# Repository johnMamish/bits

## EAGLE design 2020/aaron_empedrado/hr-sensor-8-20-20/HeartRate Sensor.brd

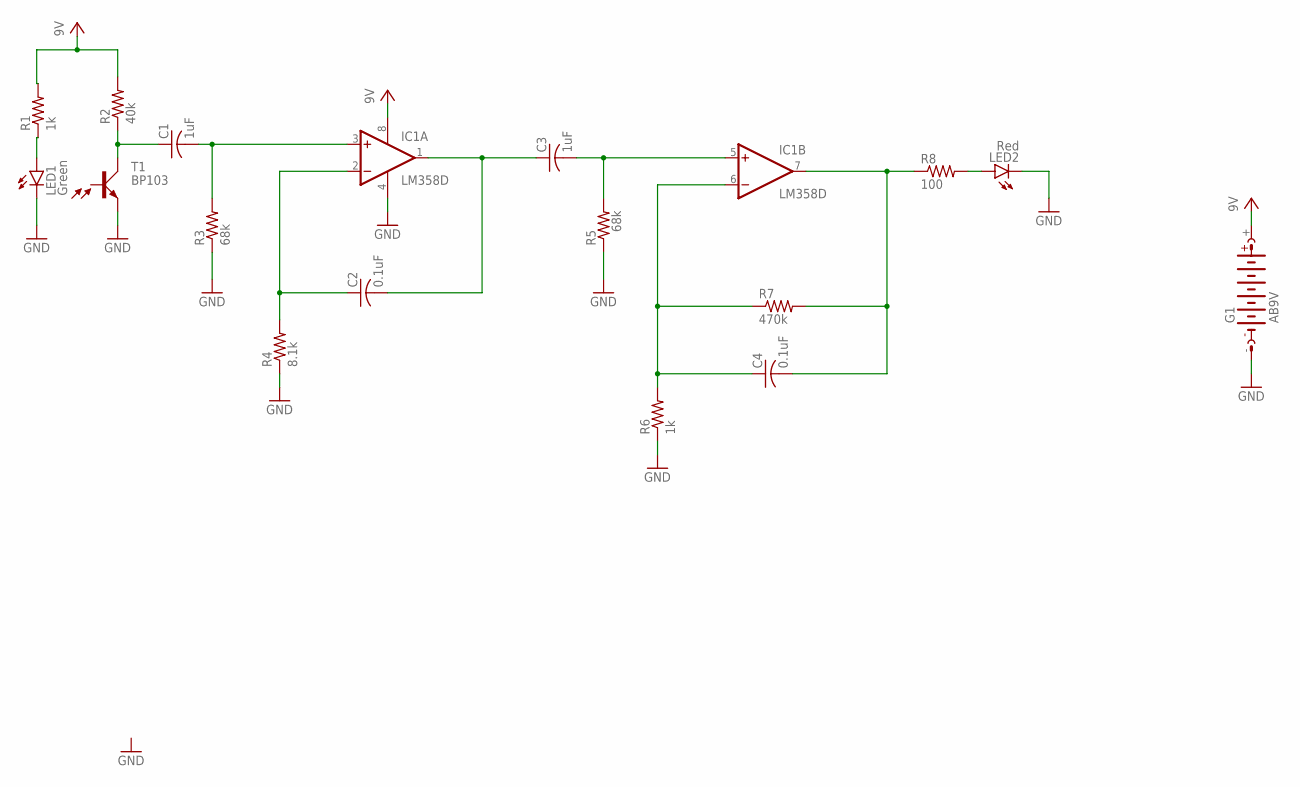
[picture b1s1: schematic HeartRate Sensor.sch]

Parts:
C1, C3: 1uF; C0805
C2, C4: 0.1uF; C0805
G1: AB9V
IC1: LM358D; SO08
LED1: Green; SMARTLED-TTW
LED2: Red; SMARTLED-TTW
R1, R6: 1k; R0805
R2: 40k; R0805
R3, R5: 68k; R0805
R4: 8.1k; R0805
R7: 470k; R0805
R8: 100; R0805
T1: BP103

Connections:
GND: G1.-, IC1.4 (V-), LED1.C@1 (C), LED2.C@1 (C), R3.1, R4.1, R5.1, R6.1, T1.E
unnamed: C1.2, IC1.3 (+IN), R3.2
unnamed: C2.1, IC1.2 (-IN), R4.2
unnamed: C3.2, IC1.5 (+IN), R5.2
unnamed: C2.2, C3.1, IC1.1 (OUT)
unnamed: C4.1, IC1.6 (-IN), R6.2, R7.1
unnamed: C4.2, IC1.7 (OUT), R7.2, R8.1
unnamed: LED2.A@1 (A), R8.2
unnamed: LED1.A@1 (A), R1.1
unnamed: C1.1, R2.1, T1.C
VCC: G1.+, IC1.8 (V+), R1.2, R2.2

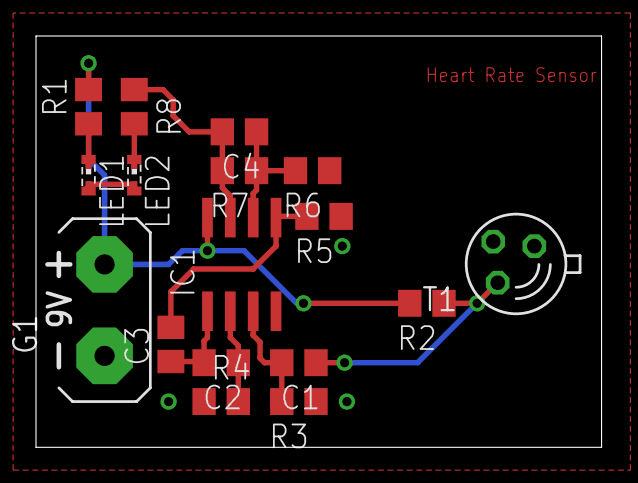
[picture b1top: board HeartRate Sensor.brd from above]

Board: 2 copper layers, 31.4 x 22.9 mm, 17 parts (0 on the bottom side), 11 nets.

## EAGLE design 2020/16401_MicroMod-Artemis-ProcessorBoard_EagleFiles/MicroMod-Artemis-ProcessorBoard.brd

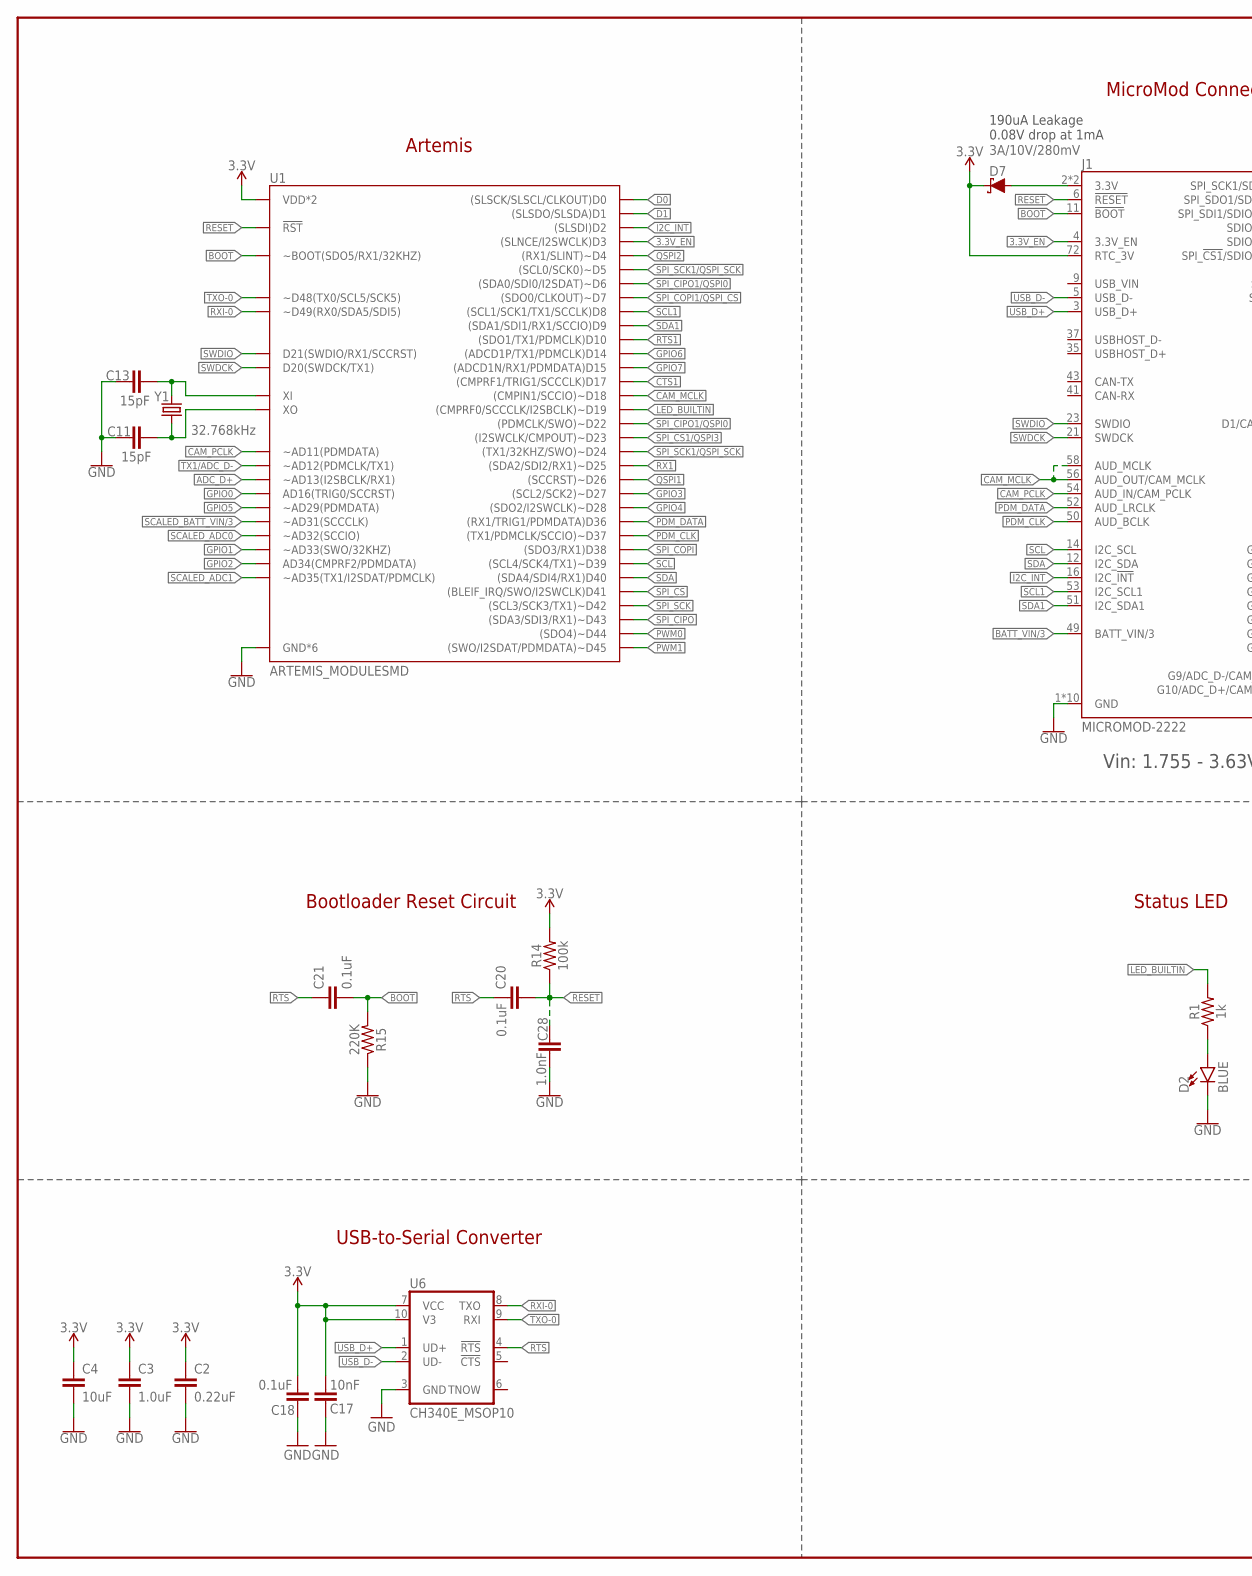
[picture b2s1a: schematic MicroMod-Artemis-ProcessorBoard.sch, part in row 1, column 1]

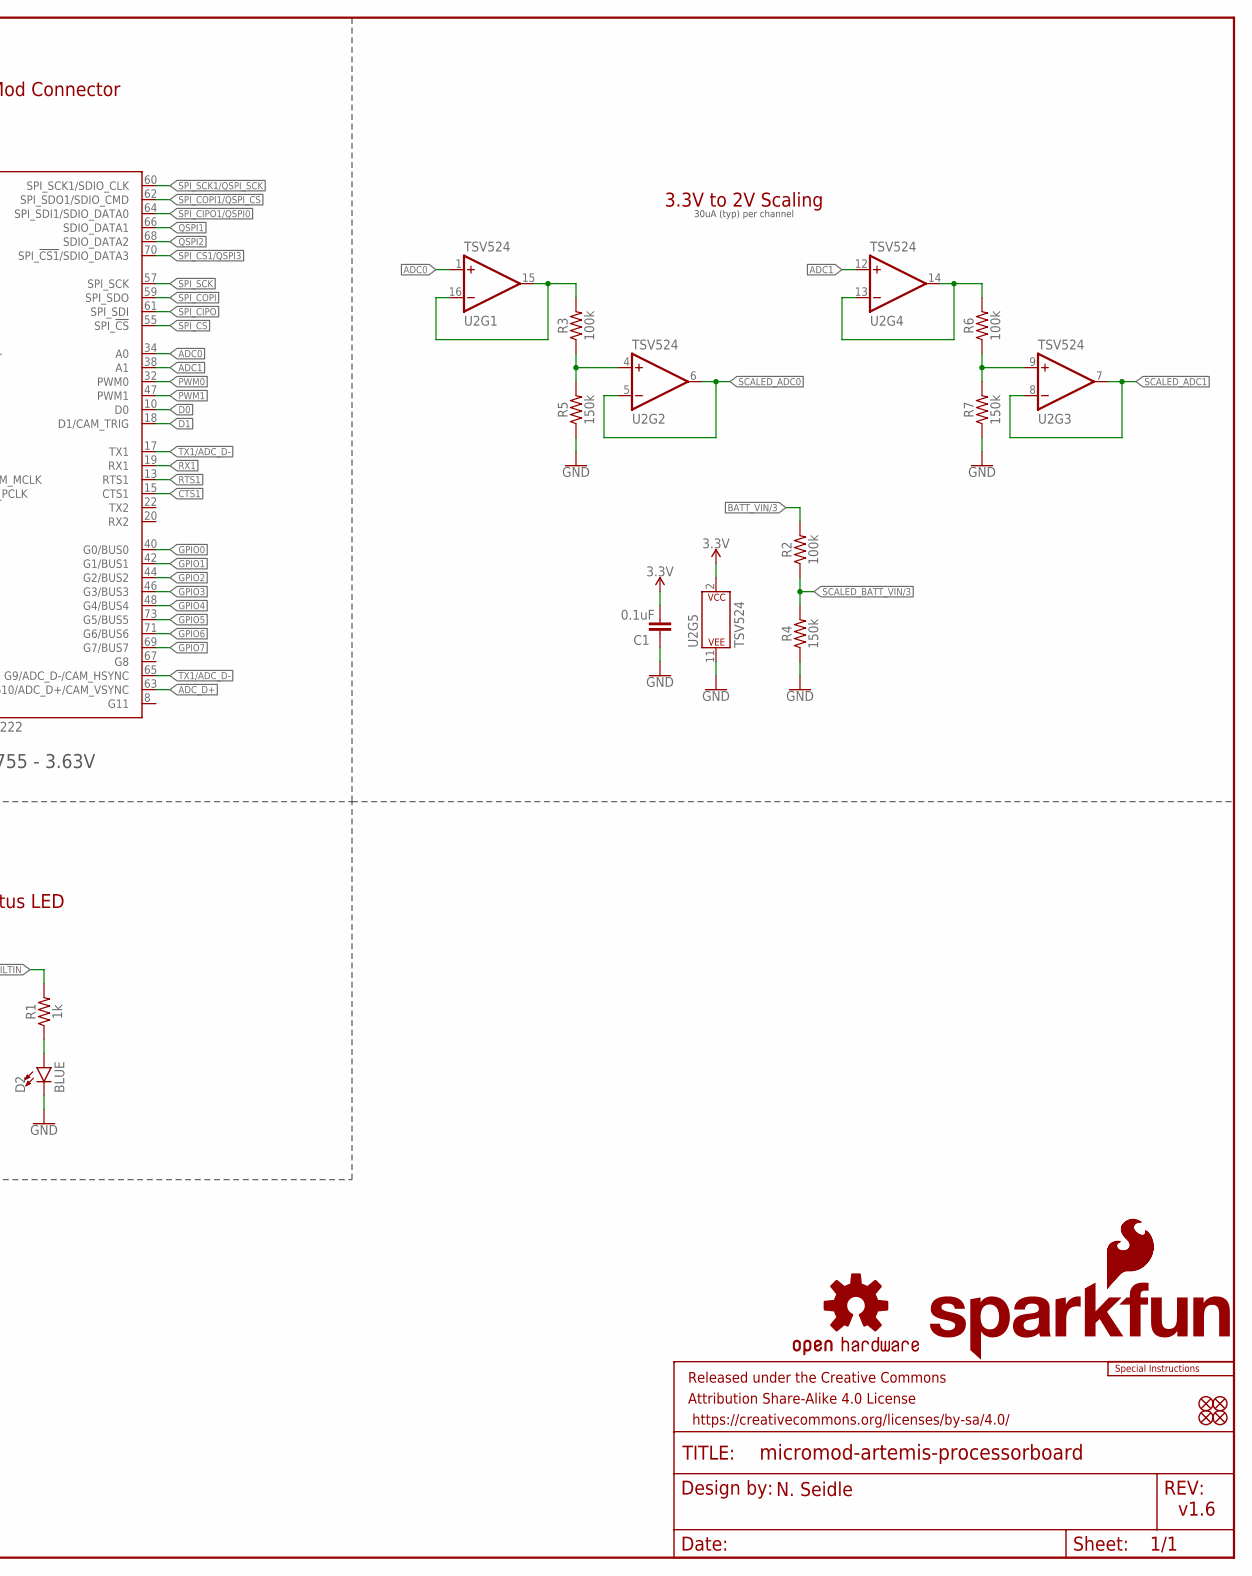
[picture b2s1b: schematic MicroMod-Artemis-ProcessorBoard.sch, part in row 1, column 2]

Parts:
C1, C18, C20, C21: 0.1uF; 0402-TIGHT
C2: 0.22uF; 0402-TIGHT
C3: 1.0uF; 0402-TIGHT
C4: 10uF; 0603
C11, C13: 15pF; 0402-TIGHT
C17: 10nF; 0402-TIGHT
C28: 1.0nF; 0402-TIGHT
D2: BLUE; LED-0603
D7: 3A/10V/280mV; SOD-323
FD1, FD2, FD3, FD4: FIDUCIALUFIDUCIAL; FIDUCIAL-MICRO
FRAME1: FRAME-LEDGER; CREATIVE_COMMONS
J1: MICROMOD-2222; M.2-CARD-E-22
LOGO1: SFE_LOGO_NAME_FLAME.1_INCH; SFE_LOGO_NAME_FLAME_.1
LOGO2: SFE_LOGO_FLAME.1_INCH; SFE_LOGO_FLAME_.1
LOGO3: OSHW-LOGOMINI; OSHW-LOGO-MINI
LOGO4: SPECIAL_INSTRUCTIONS-ORDERING; ORDERING_INSTRUCTIONS
R1: 1k; 0402-TIGHT
R2, R3, R6, R14: 100k; 0402-TIGHT
R4, R5, R7: 150k; 0402-TIGHT
R15: 220K; 0402-TIGHT
U1: ARTEMIS_MODULESMD; ARTEMIS_FP
U2: TSV524; QFN-16
U6: CH340E_MSOP10; MSOP10
Y1: 32.768kHz; CRYSTAL-SMD-3.2X1.5MM

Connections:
3.3V: C1.1, C2.1, C3.1, C4.1, C17.1, C18.1, D7.C, J1.72 (RTC_3V), R14.2, U1.VDD@36 (VDD*2), U1.VDD@37 (VDD*2), U2.2 (V+), U6.7 (VCC), U6.10 (V3)
3.3V_EN: J1.4 (3.3V_EN), U1.D3 ((SLNCE/I2SWCLK)D3)
3.3V_MAIN: D7.A, J1.2 (3.3V), J1.74 (3.3V)
!RESET!: C20.2, C28.1, J1.6 (!RESET!), R14.1, U1.~RST (!RST)
!RTS: C20.1, C21.1, U6.4 (!RTS)
ADC0: J1.34 (A0), U2.1 (+IN)
ADC0_BUFF1: R3.2, U2.15 (OUT), U2.16 (-IN)
ADC0_BUFF2: R3.1, R5.2, U2.4 (+IN)
ADC1: J1.38 (A1), U2.12 (+IN)
ADC1_BUFF2: R6.1, R7.2, U2.9 (+IN)
ADC_BUFF1: R6.2, U2.13 (-IN), U2.14 (OUT)
ADC_D+: J1.63 (G10/ADC_D+/CAM_VSYNC), U1.~AD13 (~AD13(I2SBCLK/RX1))
BATT_VIN/3: J1.49 (BATT_VIN/3), R2.2
BOOT: C21.2, J1.11 (!BOOT!), R15.2, U1.BOOT (~BOOT(SDO5/RX1/32KHZ))
CAM_MCLK: J1.56 (AUD_OUT/CAM_MCLK), J1.58 (AUD_MCLK), U1.~D18 ((CMPIN1/SCCIO)~D18)
CAM_PCLK: J1.54 (AUD_IN/CAM_PCLK), U1.~AD11 (~AD11(PDMDATA))
CTS1: J1.15 (CTS1), U1.D17 ((CMPRF1/TRIG1/SCCCLK)D17)
D0: J1.10 (D0), U1.D0 ((SLSCK/SLSCL/CLKOUT)D0)
D1: J1.18 (D1/CAM_TRIG), U1.D1 ((SLSDO/SLSDA)D1)
GND: C1.2, C2.2, C3.2, C4.2, C11.1, C13.1, C17.2, C18.2, C28.2, D2.C, J1.1 (GND), J1.7 (GND), J1.33 (GND), J1.36 (GND), J1.39 (GND), J1.45 (GND), J1.75 (GND), J1.GND1 (GND), J1.GND2 (GND), J1.GND3 (GND), R4.1, R5.1, R7.1, R15.1, U1.GND@1 (GND*6), U1.GND@22 (GND*6), U1.GND@38 (GND*6), U1.GND@39 (GND*6), U1.GND@47 (GND*6), U1.GND@59 (GND*6), U2.11 (V-), U6.3 (GND)
GPIO0: J1.40 (G0/BUS0), U1.AD16 (AD16(TRIG0/SCCRST))
GPIO1: J1.42 (G1/BUS1), U1.~AD33/SWO (~AD33(SWO/32KHZ))
GPIO2: J1.44 (G2/BUS2), U1.AD34 (AD34(CMPRF2/PDMDATA))
GPIO3: J1.46 (G3/BUS3), U1.~D27 ((SCL2/SCK2)~D27)
GPIO4: J1.48 (G4/BUS4), U1.~D28 ((SDO2/I2SWCLK)~D28)
GPIO5: J1.73 (G5/BUS5), U1.~AD29 (~AD29(PDMDATA))
GPIO6: J1.71 (G6/BUS6), U1.D14 ((ADCD1P/TX1/PDMCLK)D14)
GPIO7: J1.69 (G7/BUS7), U1.D15 ((ADCD1N/RX1/PDMDATA)D15)
I2C_!INT!: J1.16 (I2C_!INT!), U1.D2 ((SLSDI)D2)
LED_BUILTIN: R1.2, U1.~D19 ((CMPRF0/SCCCLK/I2SBCLK)~D19)
unnamed: D2.A, R1.1
unnamed: C13.2, U1.XI, Y1.P$1 (1)
unnamed: C11.2, U1.XO, Y1.P$2 (2)
PDM_CLK: J1.50 (AUD_BCLK), U1.~D37 ((TX1/PDMCLK/SCCIO)~D37)
PDM_DATA: J1.52 (AUD_LRCLK), U1.D36 ((RX1/TRIG1/PDMDATA)D36)
PWM0: J1.32 (PWM0), U1.~D44 ((SDO4)~D44)
PWM1: J1.47 (PWM1), U1.~D45 ((SWO/I2SDAT/PDMDATA)~D45)
QSPI1: J1.66 (SDIO_DATA1), U1.~D26 ((SCCRST)~D26)
QSPI2: J1.68 (SDIO_DATA2), U1.~D4 ((RX1/SLINT)~D4)
RTS1: J1.13 (RTS1), U1.D10 ((SDO1/TX1/PDMCLK)D10)
RX1: J1.19 (RX1), U1.~D25 ((SDA2/SDI2/RX1)~D25)
RXI-0: U1.RXI-0 (~D49(RX0/SDA5/SDI5)), U6.8 (TXO)
SCALED_ADC0: U1.~AD32 (~AD32(SCCIO)), U2.5 (-IN), U2.6 (OUT)
SCALED_ADC1: U1.~AD35 (~AD35(TX1/I2SDAT/PDMCLK)), U2.7 (OUT), U2.8 (-IN)
SCALED_BATT_VIN/3: R2.1, R4.2, U1.~AD31 (~AD31(SCCCLK))
SCL: J1.14 (I2C_SCL), U1.~D39 ((SCL4/SCK4/TX1)~D39)
SCL1: J1.53 (I2C_SCL1), U1.D8 ((SCL1/SCK1/TX1/SCCLK)D8)
SDA: J1.12 (I2C_SDA), U1.D40 ((SDA4/SDI4/RX1)D40)
SDA1: J1.51 (I2C_SDA1), U1.D9 ((SDA1/SDI1/RX1/SCCIO)D9)
SPI_!CS1!/QSPI3: J1.70 (SPI_!CS1!/SDIO_DATA3), U1.~D23 ((I2SWCLK/CMPOUT)~D23)
SPI_!CS!: J1.55 (SPI_!CS!), U1.D41 ((BLEIF_IRQ/SWO/I2SWCLK)D41)
SPI_CIPO: J1.61 (SPI_SDI), U1.~D43 ((SDA3/SDI3/RX1)~D43)
SPI_CIPO1/QSPI0: J1.64 (SPI_SDI1/SDIO_DATA0), U1.~D6 ((SDA0/SDI0/I2SDAT)~D6), U1.~D22 ((PDMCLK/SWO)~D22)
SPI_COPI: J1.59 (SPI_SDO), U1.D38 ((SDO3/RX1)D38)
SPI_COPI1/QSPI_!CS!: J1.62 (SPI_SDO1/SDIO_CMD), U1.D7 ((SDO0/CLKOUT)~D7)
SPI_SCK: J1.57 (SPI_SCK), U1.~D42 ((SCL3/SCK3/TX1)~D42)
SPI_SCK1/QSPI_SCK: J1.60 (SPI_SCK1/SDIO_CLK), U1.~D5 ((SCL0/SCK0)~D5), U1.~D24 ((TX1/32KHZ/SWO)~D24)
SWDCK: J1.21 (SWDCK), U1.SWDCK (D20(SWDCK/TX1))
SWDIO: J1.23 (SWDIO), U1.SWDIO (D21(SWDIO/RX1/SCCRST))
TX1/ADC_D-: J1.17 (TX1), J1.65 (G9/ADC_D-/CAM_HSYNC), U1.~AD12 (~AD12(PDMCLK/TX1))
TXO-0: U1.TXO-0 (~D48(TX0/SCL5/SCK5)), U6.9 (RXI)
USB_D+: J1.3 (USB_D+), U6.1 (UD+)
USB_D-: J1.5 (USB_D-), U6.2 (UD-)

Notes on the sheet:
USB-to-Serial Converter
Bootloader Reset Circuit
MicroMod Connector
3.3V to 2V Scaling
v1.6
N. Seidle
Artemis
Status LED
Vin: 1.755 - 3.63V
190uA Leakage 0.08V drop at 1mA
30uA (typ) per channel

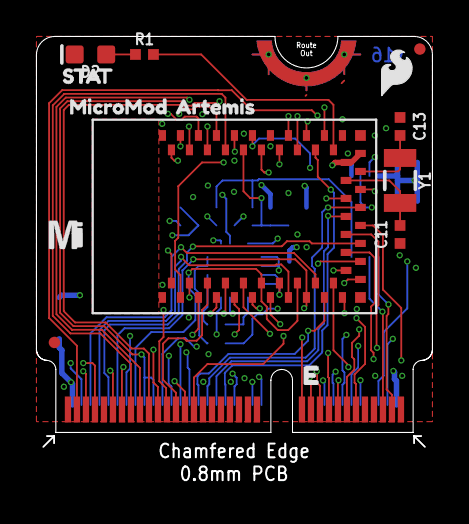
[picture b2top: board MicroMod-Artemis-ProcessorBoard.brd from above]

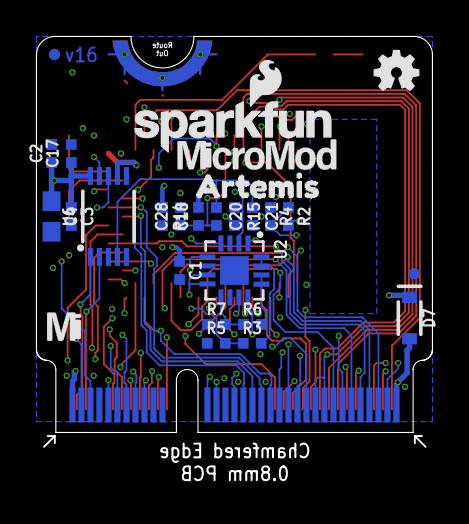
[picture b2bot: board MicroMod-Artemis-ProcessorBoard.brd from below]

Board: 4 copper layers, 21.9 x 25.0 mm, 43 parts (27 on the bottom side), 63 nets.

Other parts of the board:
U$1, U$7: MICROMOD_MI_LOGO_.35
U$2: ARTEMIS0
U$3: MICROMOD1
U$4: STAT_TO_32
U$5: MICROMOD_LOGO_.35
U$6: ARTEMIS2

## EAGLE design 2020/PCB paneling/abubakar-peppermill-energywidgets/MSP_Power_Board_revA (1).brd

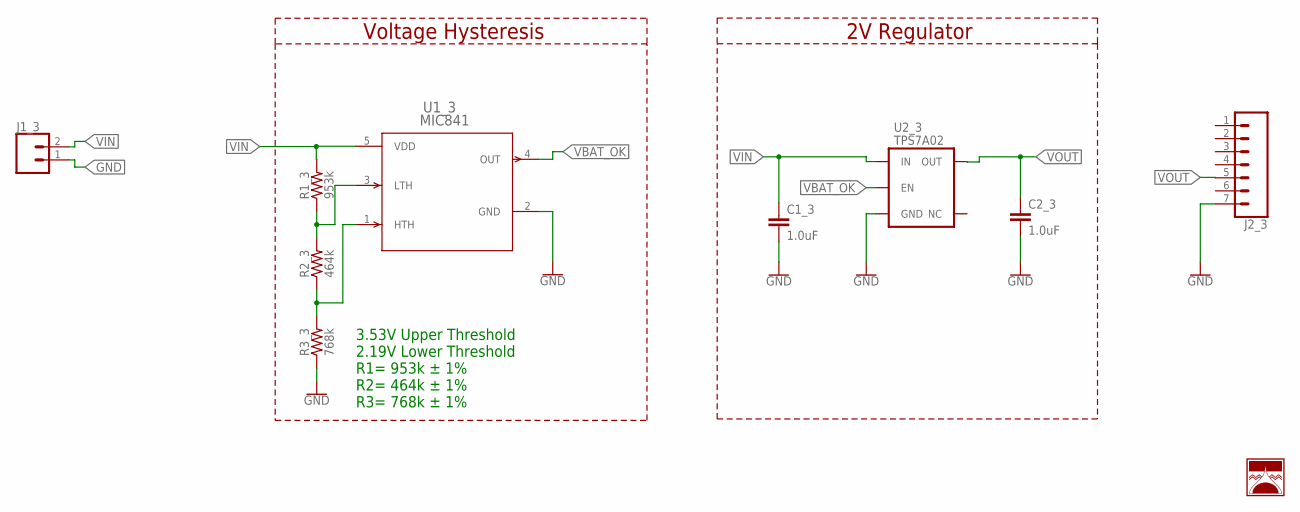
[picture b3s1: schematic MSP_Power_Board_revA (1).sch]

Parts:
C1_3, C2_3: 1.0uF; 0603
J1_3: CONN_02; 1X02
J2_3: CONN_07; 1X07
R1_3: 953k; 0603
R2_3: 464k; 0603
R3_3: 768k; 0603
U1_3: MIC841; SC-70_C5_MCH
U2_3: TPS7A02; SOT23-5
U$1_3: KAMOAMOA_LOGO_4X4MM; LOGO_4X4MM

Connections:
GND: C1_3.2, C2_3.2, J1_3.1, J2_3.7, R3_3.1, U1_3.2 (GND), U2_3.2 (GND)
unnamed: R1_3.1, R2_3.2, U1_3.3 (LTH)
unnamed: R2_3.1, R3_3.2, U1_3.1 (HTH)
VBAT_OK: U1_3.4 (OUT), U2_3.3 (EN)
VIN: C1_3.1, J1_3.2, R1_3.2, U1_3.5 (VDD), U2_3.1 (IN)
VOUT: C2_3.1, J2_3.5, U2_3.5 (OUT)

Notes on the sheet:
Voltage Hysteresis
3.53V Upper Threshold 2.19V Lower Threshold R1= 953k ± 1% R2= 464k ± 1% R3= 768k ± 1%
2V Regulator

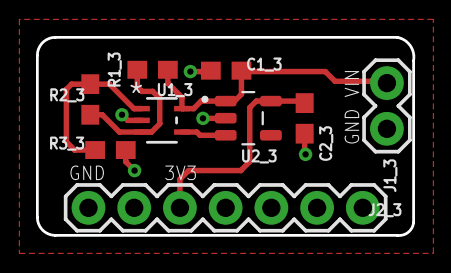
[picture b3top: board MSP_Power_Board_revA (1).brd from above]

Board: 2 copper layers, 20.9 x 11.0 mm, 10 parts (0 on the bottom side), 6 nets.

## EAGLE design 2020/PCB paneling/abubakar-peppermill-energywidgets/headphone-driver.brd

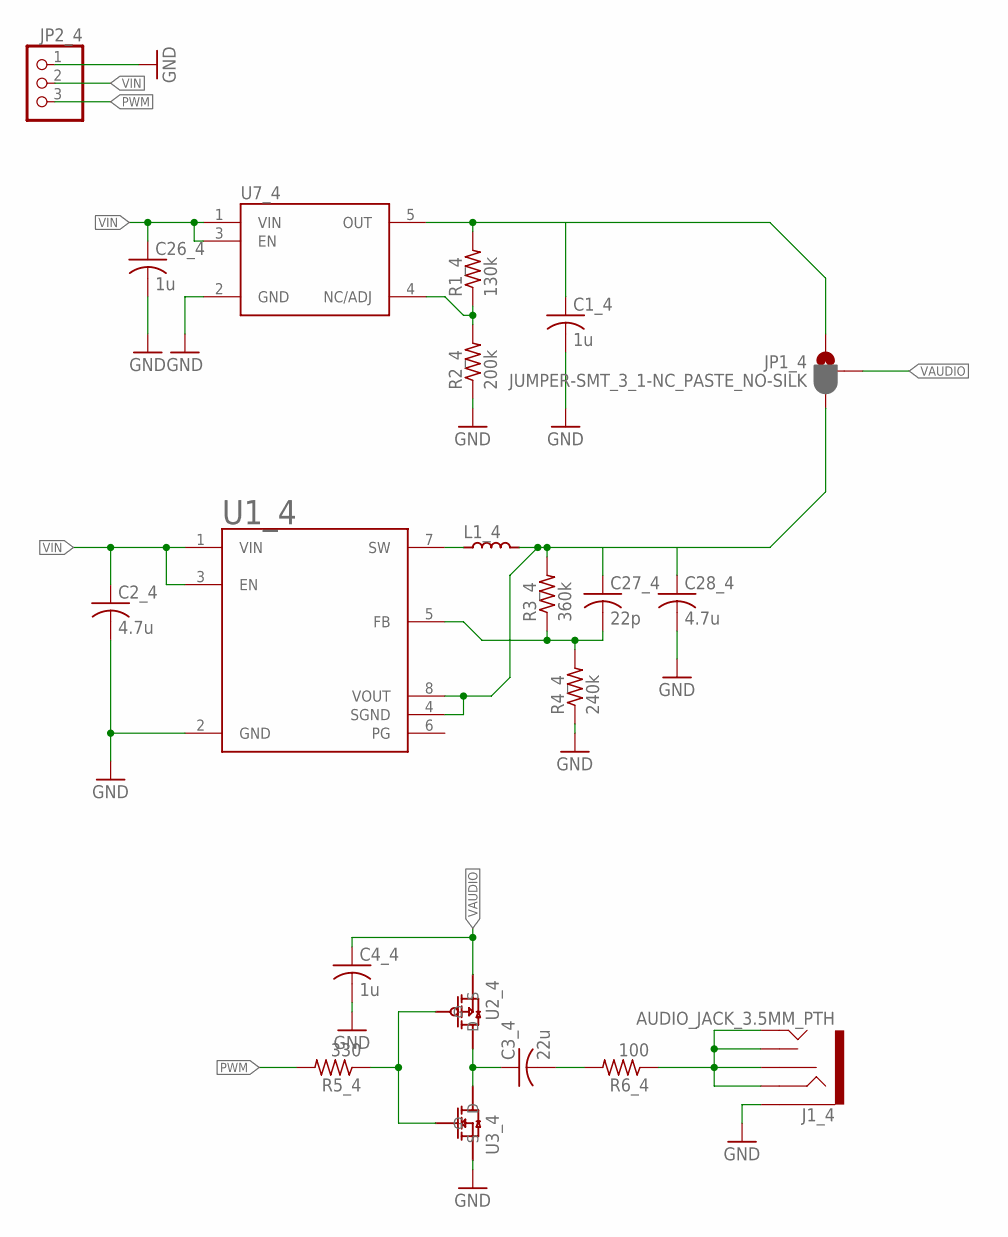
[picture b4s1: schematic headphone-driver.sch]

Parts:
C1_4, C4_4, C26_4: 1u; C0603; MFR_PN CL10B105KA8NNNC
C2_4, C28_4: 4.7u; C0603; MFR_PN CL10A475KA8NQNC
C3_4: 22u; C0805; MFR_PN GRM21BR61E226ME44L
C27_4: 22p; C0402; MFR_PN C0603C220J5GACTU
J1_4: AUDIO_JACK_3.5MM_PTH; AUDIO-JACK
JP1_4: JUMPER-SMT_3_1-NC_PASTE_NO-SILK; SMT-JUMPER_3_1-NC_PASTE_NO-SILK
JP2_4: PINHD-1X3; 1X03
L1_4: 22u; LQH3NPNXXXXMEX; MFR_PN LQH3NPN220MJRL
R1_4: 130k; R0603; MFR_PN ERJ-3GEYJ134V
R2_4: 200k; R0603; MFR_PN ERJ-3GEYJ204V
R3_4: 360k; R0603; MFR_PN ERJ-3GEYJ364V
R4_4: 240k; R0603; MFR_PN ERJ-3GEYJ244V
R5_4: 330; R0603; MFR_PN RC0603FR-07330RL
R6_4: 100; R0603; MFR_PN RC0603JR-07100RL
U1_4: TPS62120; SOP65P280X145-8N; MFR_PN TPS62120
U2_4: TP2104K1-G
U3_4: TN2106K1-G
U7_4: MIC5225; MFR_PN MIC5225YM5

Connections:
BUCK_OUT: C27_4.1, C28_4.1, JP1_4.3, L1_4.P$2, R3_4.2, U1_4.4 (SGND), U1_4.8 (VOUT)
GND: C1_4.2, C2_4.2, C4_4.2, C26_4.2, C28_4.2, J1_4.SLEEVE, JP2_4.1, R2_4.1, R4_4.1, U1_4.2 (GND), U3_4.S, U7_4.2 (GND)
LINEAR_OUT: C1_4.1, JP1_4.1, R1_4.2, U7_4.5 (OUT)
unnamed: R1_4.1, R2_4.2, U7_4.4 (NC/ADJ)
unnamed: R5_4.1, U2_4.G, U3_4.G
unnamed: C3_4.1, U2_4.D, U3_4.D
unnamed: C27_4.2, R3_4.1, R4_4.2, U1_4.5 (FB)
unnamed: L1_4.P$1, U1_4.7 (SW)
unnamed: C3_4.2, R6_4.2
unnamed: J1_4.RING, J1_4.RSH, J1_4.TIP, J1_4.TSH, R6_4.1
PWM: JP2_4.3, R5_4.2
VAUDIO: C4_4.1, JP1_4.2, U2_4.S
VIN: C2_4.1, C26_4.1, JP2_4.2, U1_4.1 (VIN), U1_4.3 (EN), U7_4.1 (VIN), U7_4.3 (EN)

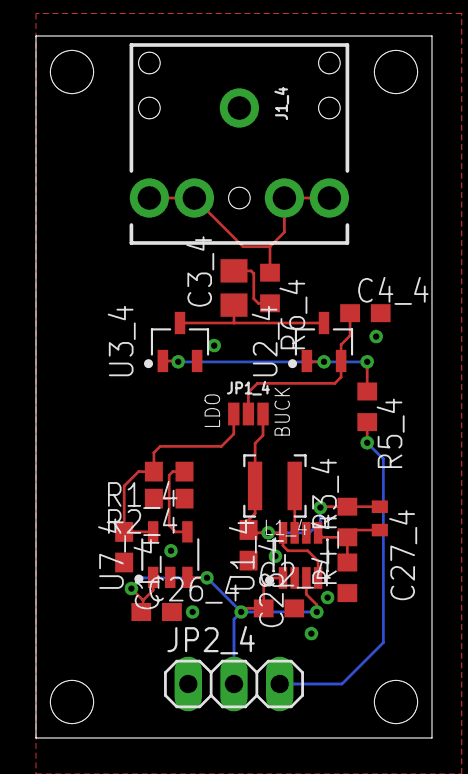
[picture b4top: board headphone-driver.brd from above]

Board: 2 copper layers, 22.0 x 39.0 mm, 21 parts (0 on the bottom side), 13 nets.

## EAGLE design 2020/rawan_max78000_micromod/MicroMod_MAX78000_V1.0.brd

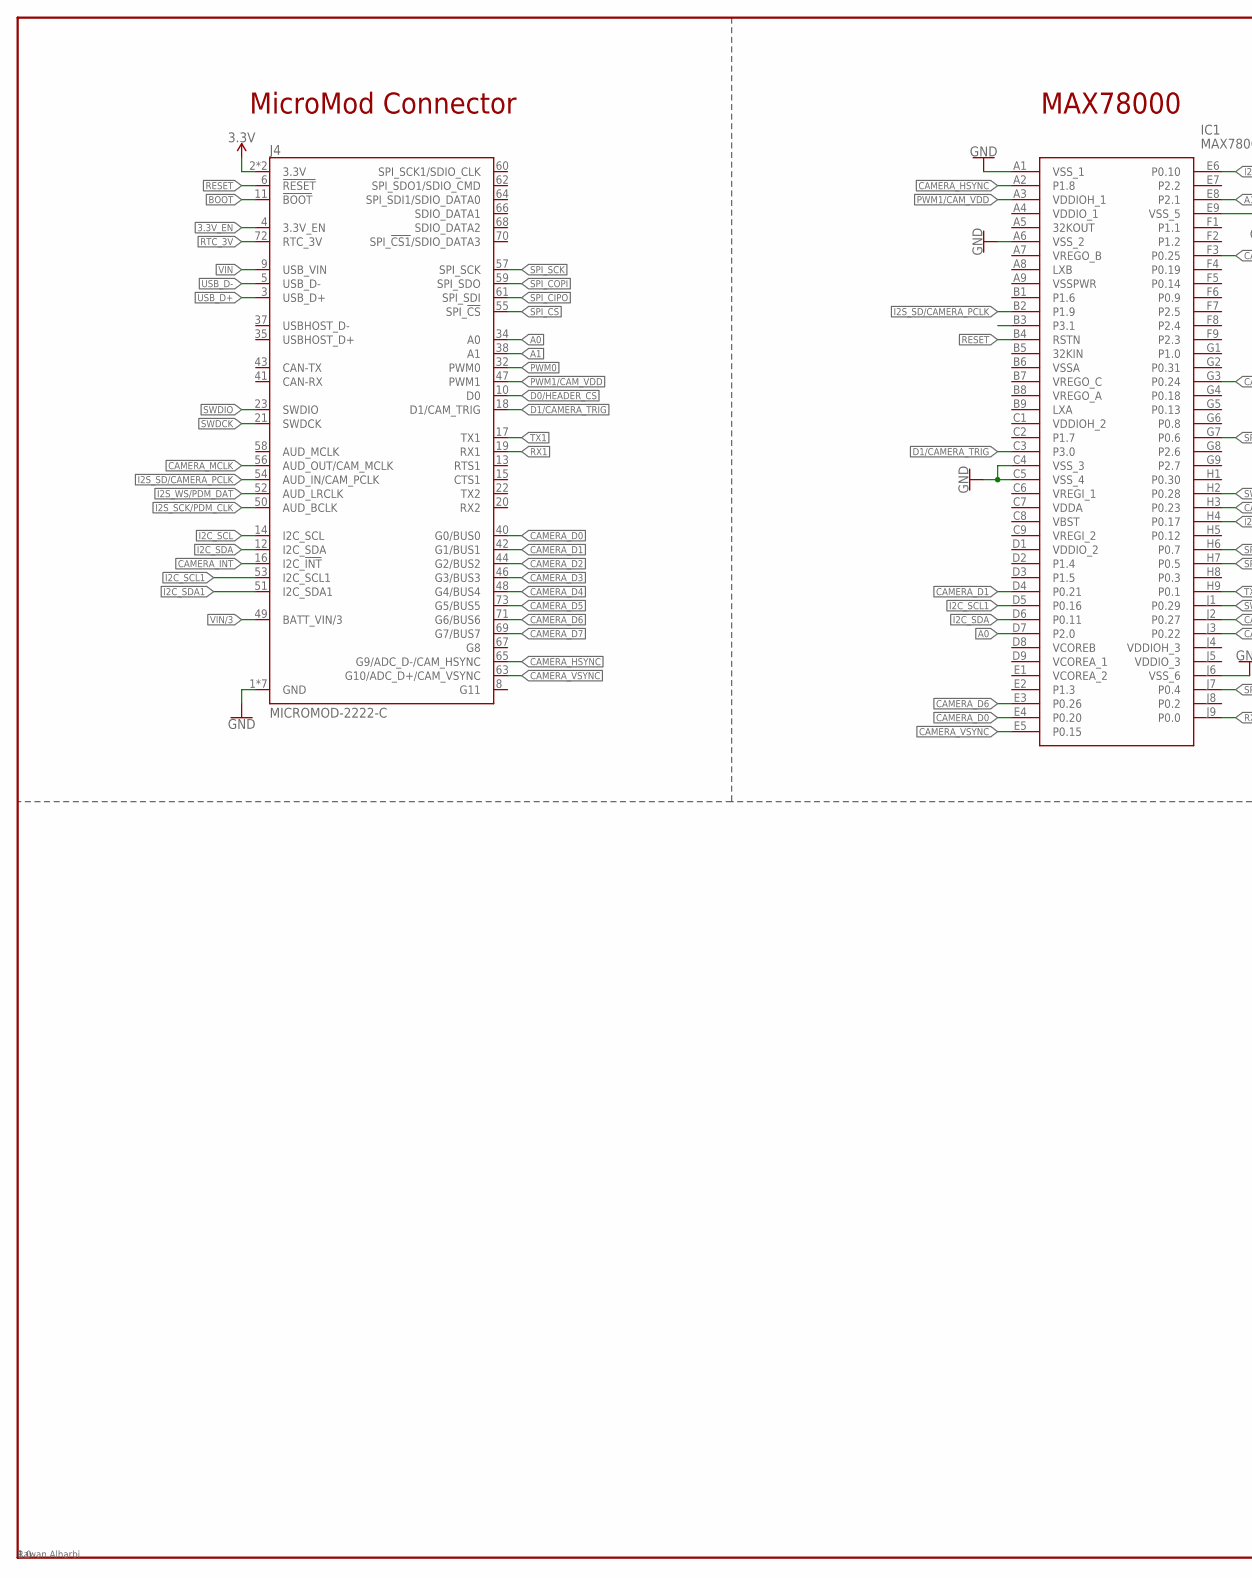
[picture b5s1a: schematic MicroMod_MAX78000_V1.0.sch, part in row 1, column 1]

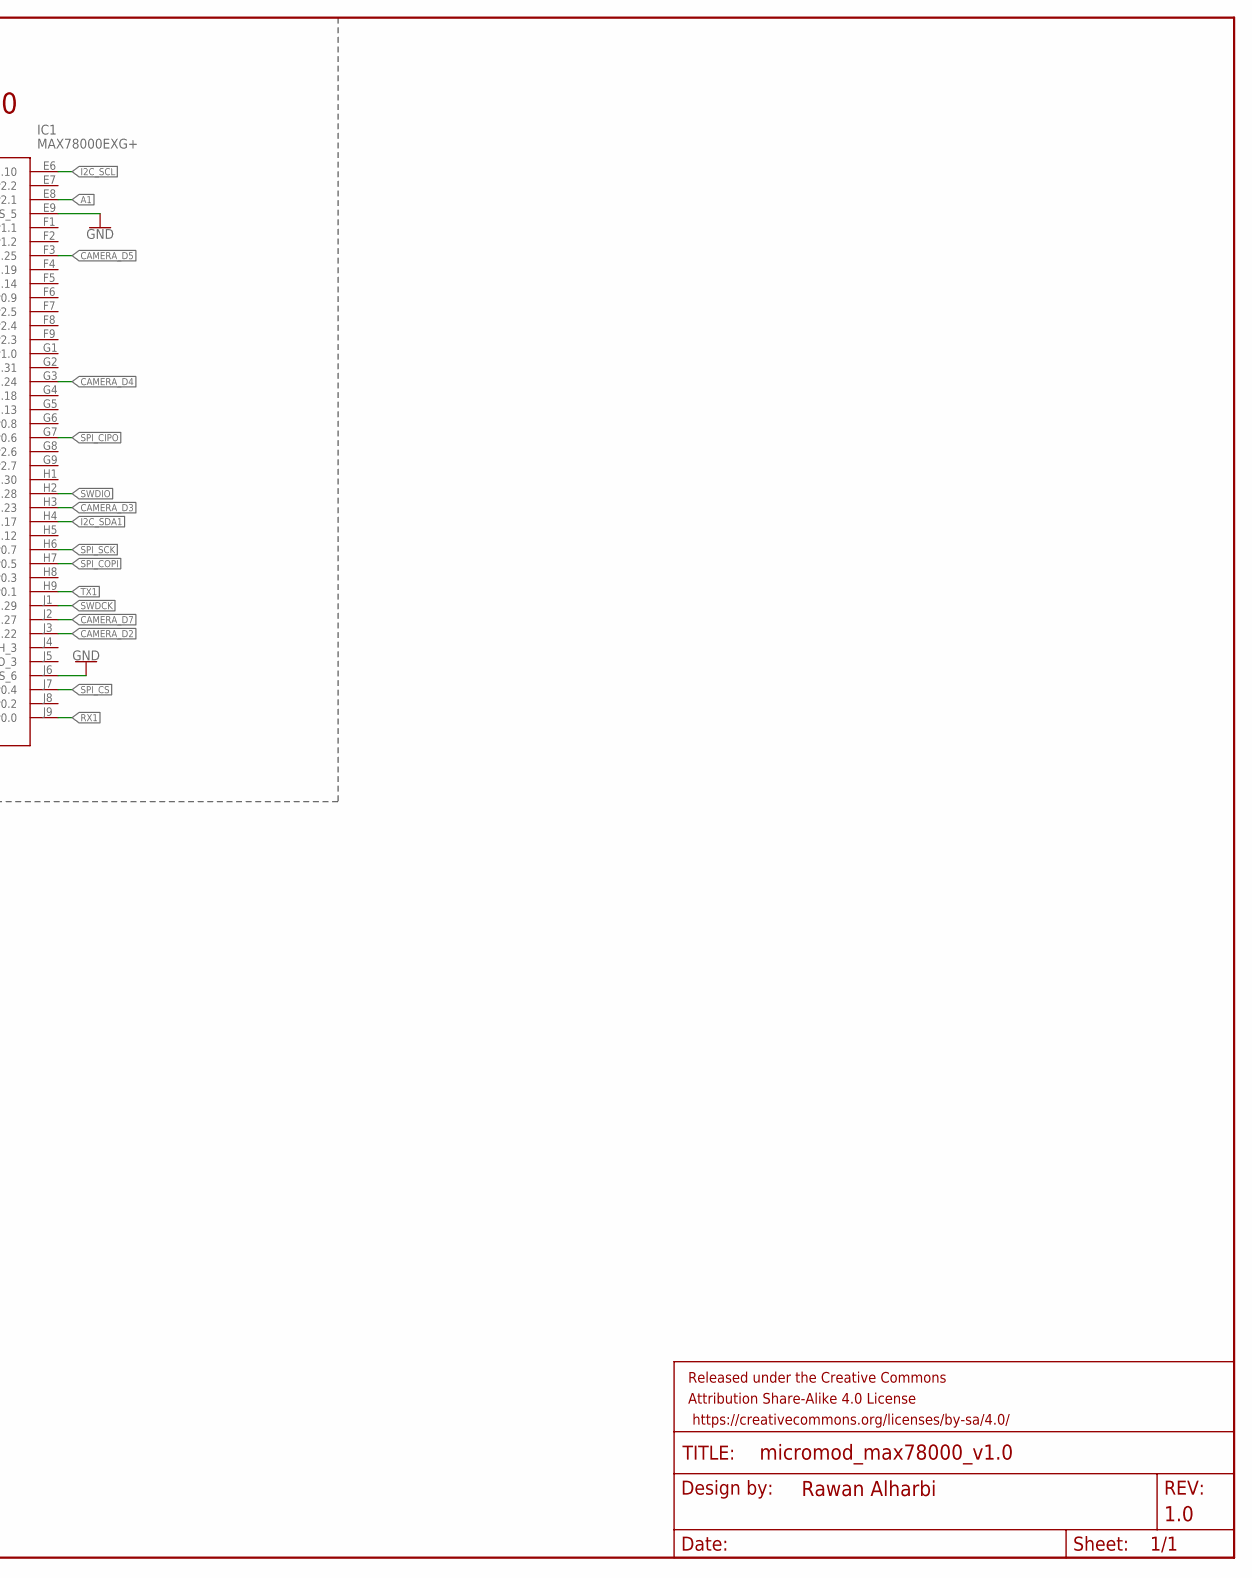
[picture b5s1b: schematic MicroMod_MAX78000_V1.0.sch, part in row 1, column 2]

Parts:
FRAME1: FRAME-LEDGER; CREATIVE_COMMONS
IC1: MAX78000EXG+; BGA81C80P9X9_800X800X130
J4: MICROMOD-2222-C; M.2-CONNECTOR-E

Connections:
3.3V: J4.2 (3.3V), J4.74 (3.3V)
3.3V_EN: J4.4 (3.3V_EN)
!BOOT!: J4.11 (!BOOT!)
!RESET!: IC1.B4 (RSTN), J4.6 (!RESET!)
A0: IC1.D7 (P2.0), J4.34 (A0)
A1: IC1.E8 (P2.1), J4.38 (A1)
CAMERA_D0: IC1.E4 (P0.20), J4.40 (G0/BUS0)
CAMERA_D1: IC1.D4 (P0.21), J4.42 (G1/BUS1)
CAMERA_D2: IC1.J3 (P0.22), J4.44 (G2/BUS2)
CAMERA_D3: IC1.H3 (P0.23), J4.46 (G3/BUS3)
CAMERA_D4: IC1.G3 (P0.24), J4.48 (G4/BUS4)
CAMERA_D5: IC1.F3 (P0.25), J4.73 (G5/BUS5)
CAMERA_D6: IC1.E3 (P0.26), J4.71 (G6/BUS6)
CAMERA_D7: IC1.J2 (P0.27), J4.69 (G7/BUS7)
CAMERA_HSYNC: IC1.A2 (P1.8), J4.65 (G9/ADC_D-/CAM_HSYNC)
CAMERA_INT: J4.16 (I2C_!INT!)
CAMERA_MCLK: J4.56 (AUD_OUT/CAM_MCLK)
CAMERA_VSYNC: IC1.E5 (P0.15), J4.63 (G10/ADC_D+/CAM_VSYNC)
D0/HEADER_!CS!: J4.10 (D0)
D1/CAMERA_TRIG: IC1.C3 (P3.0), J4.18 (D1/CAM_TRIG)
GND: IC1.A1 (VSS_1), IC1.A6 (VSS_2), IC1.C4 (VSS_3), IC1.C5 (VSS_4), IC1.E9 (VSS_5), IC1.J6 (VSS_6), J4.1 (GND), J4.7 (GND), J4.33 (GND), J4.36 (GND), J4.39 (GND), J4.45 (GND), J4.75 (GND)
I2C_SCL: IC1.E6 (P0.10), J4.14 (I2C_SCL)
I2C_SCL1: IC1.D5 (P0.16), J4.53 (I2C_SCL1)
I2C_SDA: IC1.D6 (P0.11), J4.12 (I2C_SDA)
I2C_SDA1: IC1.H4 (P0.17), J4.51 (I2C_SDA1)
I2S_SCK/PDM_CLK: J4.50 (AUD_BCLK)
I2S_SD/CAMERA_PCLK: IC1.B2 (P1.9), J4.54 (AUD_IN/CAM_PCLK)
I2S_WS/PDM_DAT: J4.52 (AUD_LRCLK)
PWM0: J4.32 (PWM0)
PWM1/CAM_VDD: IC1.A3 (VDDIOH_1), J4.47 (PWM1)
RTC_3V: J4.72 (RTC_3V)
RX1: IC1.J9 (P0.0), J4.19 (RX1)
SPI_!CS!: IC1.J7 (P0.4), J4.55 (SPI_!CS!)
SPI_CIPO: IC1.G7 (P0.6), J4.61 (SPI_SDI)
SPI_COPI: IC1.H7 (P0.5), J4.59 (SPI_SDO)
SPI_SCK: IC1.H6 (P0.7), J4.57 (SPI_SCK)
SWDCK: IC1.J1 (P0.29), J4.21 (SWDCK)
SWDIO: IC1.H2 (P0.28), J4.23 (SWDIO)
TX1: IC1.H9 (P0.1), J4.17 (TX1)
USB_D+: J4.3 (USB_D+)
USB_D-: J4.5 (USB_D-)
VIN: J4.9 (USB_VIN)
VIN/3: J4.49 (BATT_VIN/3)

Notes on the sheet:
MicroMod Connector
MAX78000

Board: 2 copper layers, 3 parts (0 on the bottom side), 30 nets, no tracks yet.

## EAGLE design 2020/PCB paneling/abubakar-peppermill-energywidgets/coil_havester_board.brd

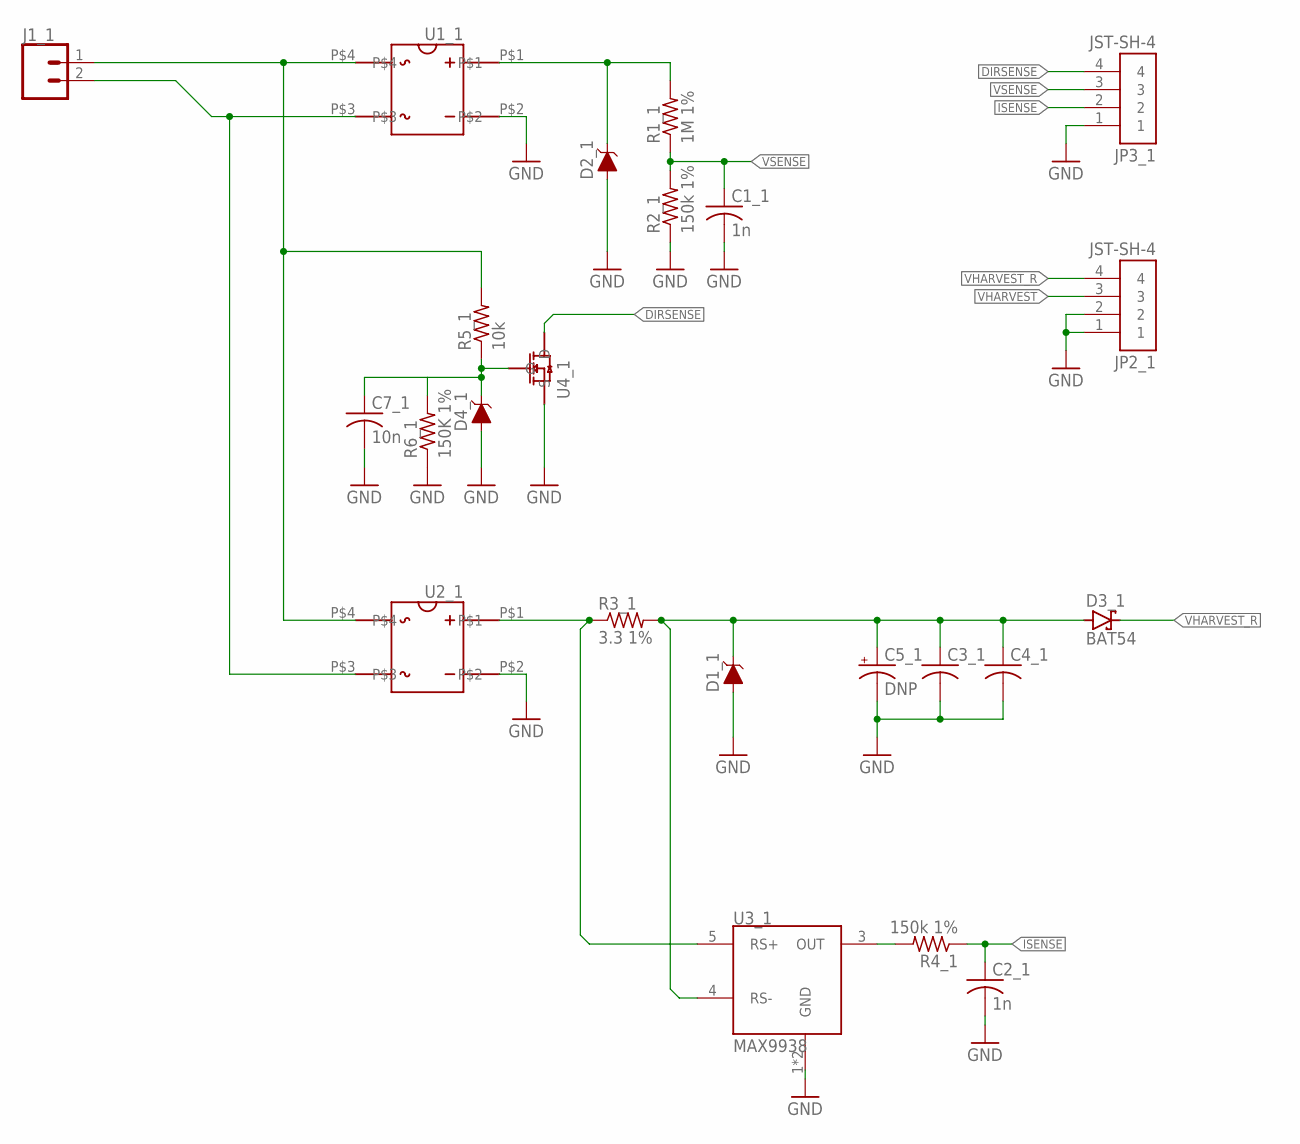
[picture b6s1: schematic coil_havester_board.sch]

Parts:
C1_1, C2_1: 1n; C0402; MFR_PN CL05B102KB5NNNC
C3_1, C4_1: C-USC1206; C1206; MFR_PN C3216X5R1E476M160AC
C5_1: DNP; E2,5-5
C7_1: 10n; C0402; MFR_PN CL05B103KB5NNNC
D1_1, D2_1: 3.3V; SOD-323; MFR_PN BZT52C15S
D3_1: BAT54; SOT23; MFR_PN BAT54
D4_1: 3.3V; SOD-323
J1_1: CONN_02-JST-2MM-SMT; JST-2-SMD; MFR_PN S2B-PH-SM4-TB(LF)(SN)
JP2_1, JP3_1: JST-SH-4; MFR_PN SM04B-SRSS-TB(LF)(SN)
R1_1: 1M 1%; R0402; MFR_PN RC0402FR-071ML
R2_1, R4_1: 150k 1%; R0402; MFR_PN RC0402FR-07150KL
R3_1: 3.3 1%; R0603; MFR_PN ERJ-3BQF3R3V
R5_1: 10k; R0402; MFR_PN RC0402FR-0710KL
R6_1: 150K 1%; R0402; MFR_PN RC0402FR-07150KL
U1_1, U2_1: CDBHD140L-G; CDBHDXX0L-G; MFR_PN CDBHD140L-G
U3_1: MAX9938; SOT23-5; MFR_PN MAX9938TEUK+T
U4_1: TN2106K1-G

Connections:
DIRSENSE: JP3_1.4, U4_1.D
GND: C1_1.2, C2_1.2, C3_1.2, C4_1.2, C5_1.-, C7_1.2, D1_1.A, D2_1.A, D4_1.A, JP2_1.1, JP2_1.2, JP3_1.1, R2_1.1, R6_1.1, U1_1.P$2, U2_1.P$2, U3_1.1 (GND), U3_1.2 (GND), U4_1.S
ISENSE: C2_1.1, JP3_1.2, R4_1.1
unnamed: J1_1.1 (2), R5_1.2, U1_1.P$4, U2_1.P$4
unnamed: J1_1.2 (1), U1_1.P$3, U2_1.P$3
unnamed: D2_1.C, R1_1.2, U1_1.P$1
unnamed: R3_1.1, U2_1.P$1, U3_1.5 (RS+)
unnamed: R4_1.2, U3_1.3 (OUT)
unnamed: C7_1.1, D4_1.C, R5_1.1, R6_1.2, U4_1.G
VHARVEST: C3_1.1, C4_1.1, C5_1.+, D1_1.C, D3_1.1 (A), JP2_1.3, R3_1.2, U3_1.4 (RS-)
VHARVEST_R: D3_1.3 (C), JP2_1.4
VSENSE: C1_1.1, JP3_1.3, R1_1.1, R2_1.2

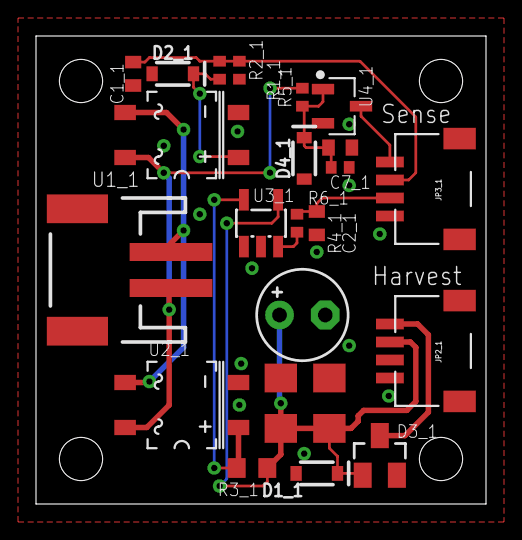
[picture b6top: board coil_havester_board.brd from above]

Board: 2 copper layers, 25.0 x 26.0 mm, 23 parts (0 on the bottom side), 12 nets.

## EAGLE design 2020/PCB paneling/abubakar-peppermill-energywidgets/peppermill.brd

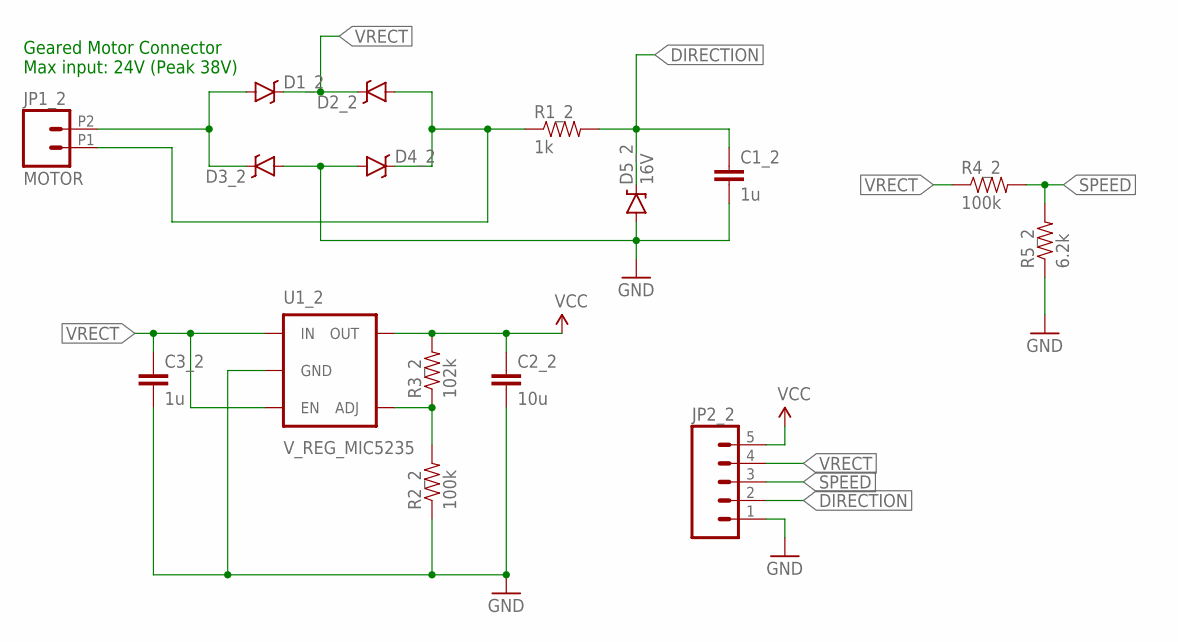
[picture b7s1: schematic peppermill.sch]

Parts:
C1_2, C3_2: 1u; 0805; DIGIKEY CL21B105KBFNNNG
C2_2: 10u; 0805; DIGIKEY CL21A106KPCLQNC
D1_2, D2_2, D3_2, D4_2: BAT20JFILM; SOD-323; DIGIKEY 1727-3877-1-ND
D5_2: 16V; SOD-123; DIGIKEY 1727-3600-1-ND
JP1_2: MOTOR; 1X02_2.54_SCREWTERM
JP2_2: M05LOCK; 1X05_LOCK
R1_2: 1k; 0805
R2_2, R4_2: 100k; 0805
R3_2: 102k; 0805
R5_2: 6.2k; 0805
U1_2: V_REG_MIC5235; SOT23-5; DIGIKEY 576-1284-1-ND

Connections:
DIRECTION: C1_2.1, D5_2.C, JP2_2.2, R1_2.2
GND: C1_2.2, C2_2.2, C3_2.2, D3_2.A, D4_2.A, D5_2.A, JP2_2.1, R2_2.1, R5_2.1, U1_2.2 (GND)
unnamed: R2_2.2, R3_2.1, U1_2.4 (ADJ)
unnamed: D1_2.A, D3_2.C, JP1_2.P2 (2)
unnamed: D2_2.A, D4_2.C, JP1_2.P1 (1), R1_2.1
SPEED: JP2_2.3, R4_2.2, R5_2.2
VCC: C2_2.1, JP2_2.5, R3_2.2, U1_2.5 (OUT)
VRECT: C3_2.1, D1_2.C, D2_2.C, JP2_2.4, R4_2.1, U1_2.1 (IN), U1_2.3 (EN)

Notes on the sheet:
Geared Motor Connector Max input: 24V (Peak 38V)

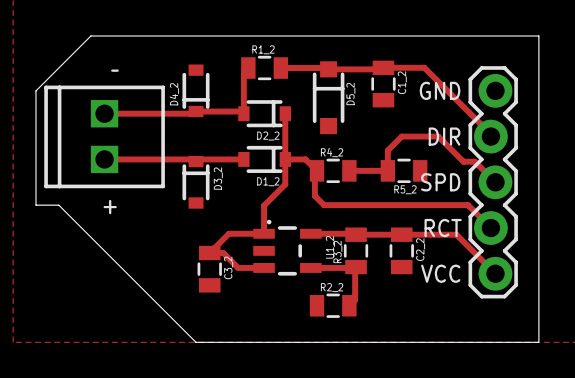
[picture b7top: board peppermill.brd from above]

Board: 2 copper layers, 27.9 x 17.0 mm, 16 parts (0 on the bottom side), 8 nets.

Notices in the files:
parts and their libraries:
SparkFun-IC-Microcontroller: Licensing: Creative Commons ShareAlike 4.0 International - https://creativecommons.org/licenses/by-sa/4.0
SparkFun-Aesthetics: Released under the Creative Commons Attribution Share-Alike 4.0 License
SparkFun-Aesthetics: https://creativecommons.org/licenses/by-sa/4.0
